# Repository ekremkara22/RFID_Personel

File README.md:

# RFID Personel Takip

RFID kart tabanli personel takip paneli. Bu repo web paneli, veritabani modeli ve ESP32/RFID cihaz entegrasyonu icin kullanilir; eski mobil uygulama kodlari devre disi birakilmistir.

## Birden fazla bilgisayarda çalışma

Her klonda bir kez çalıştırın:

```bash
git config core.hooksPath .githooks
```

Bundan sonra `git pull` ile `package-lock.json` değişirse `npm ci`, yalnız `prisma/schema.prisma` değişirse `npx prisma generate` otomatik çalışır. Veritabanı migration'ları otomatik uygulanmaz. Sunucularda bu ayar yapılmaz; deploy betikleri kurulumu zaten kendisi yapar.

## Getting Started

First, run the development server:

```bash
npm run dev
# or
yarn dev
# or
pnpm dev
# or
bun dev
```

Open [http://localhost:3000](http://localhost:3000) with your browser to see the result locally.

You can start editing the page by modifying `app/page.tsx`. The page auto-updates as you edit the file.

This project uses [`next/font`](https://nextjs.org/docs/app/building-your-application/optimizing/fonts) to automatically optimize and load [Geist](https://vercel.com/font), a new font family for Vercel.

## Learn More

To learn more about Next.js, take a look at the following resources:

- [Next.js Documentation](https://nextjs.org/docs) - learn about Next.js features and API.
- [Learn Next.js](https://nextjs.org/learn) - an interactive Next.js tutorial.

You can check out [the Next.js GitHub repository](https://github.com/vercel/next.js) - your feedback and contributions are welcome!

## Deploy on Vercel

The easiest way to deploy your Next.js app is to use the [Vercel Platform](https://vercel.com/new?utm_medium=default-template&filter=next.js&utm_source=create-next-app&utm_campaign=create-next-app-readme) from the creators of Next.js.

Check out our [Next.js deployment documentation](https://nextjs.org/docs/app/building-your-application/deploying) for more details.

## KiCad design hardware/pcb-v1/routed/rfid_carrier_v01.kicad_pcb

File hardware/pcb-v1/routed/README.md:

# RFID taşıyıcı PCB V0.2 — V4 kutu

Bu klasör V0.1 yerleşim taslağının bakır yolları çizilmiş prototip revizyonudur.
30 pin ESP32 DevKit V1 sökülebilir iki 1×15 dişi sokete takılır. Firmware GPIO
bağlantıları, V4 kart sınırı ve sekiz vida deliği korunur.

**Fiziksel prototip henüz üretilmedi veya çalıştırılmadı.** Dijital kontrollerin
sonuçları `drc.json` ve `erc.json` içindedir. Siparişten önce
aşağıdaki üç fiziksel kontrol yapılmalıdır; bu dosyalar ölçülmemiş parçaların
mekanik uyumunu garanti etmez.

## Açılacak dosyalar

- `rfid_carrier_v01.kicad_pro`: proje; dosya adı şema/PCB referanslarını korumak için sabit kaldı, revizyon V0.2'dir.
- `rfid_carrier_v01.kicad_pcb`: iki katmanlı bakır yolları, iki yüzde GND dolgusu ve
  serigrafi montaj işaretleri (pin-1 noktaları, elektrolitik `+`, D1 katot çizgisi, Q1 C/B/E).
- `rfid_carrier_v01.kicad_sch`: elektrik şeması; global hat adları PCB ile aynıdır.
- `pcb_routed.png`: gerçek PCB dosyasından KiCad ile üretilen üst yüz görünümü.
- `mechanical_1to1.svg`: kart sınırı, pedler, serigrafi ve parça zarfları; %100 baskı şablonu.
- `gerber/`: iki bakır, iki maske, iki baskı katmanı, kart sınırı, ayrı PTH/NPTH
  Excellon delik dosyaları, delik haritaları (PDF) ve `.gbrjob`.
- `drc.json`: Gerber'in üretildiği kartın KiCad DRC raporu.
- `connections.csv`, `bom.csv`: bağlantılar ve taşıyıcı kartın parça listesi.
- `native.net`: KiCad'in gerçek şemadan dışa aktardığı netlist.
- `RFID_Carrier.pretty/`, `RFID_Carrier.kicad_sym`, `*-lib-table`: proje ile taşınan yerel kütüphaneler.

Bir üst klasördeki V0.1 dosyaları ve eski inceleme PDF'si arşiv taslağıdır;
üretim için bu revizyonun dosyaları esas alınır.

## Tasarım kuralları ve değişiklikler

| Özellik | V0.2 |
|---|---|
| Kart | 128 × 58 mm, 1,6 mm, 2 katman; başlangıç 35 µm / 1 oz bakır |
| Kart koordinatları | V4 gövdesi normalize XY; X=4…132, Y=39…97 mm |
| Sinyal yolları | 0,30 mm |
| Güç yolları | 0,50 mm; GND ayrıca iki yüzeyde dolgu |
| Minimum elektriksel açıklık | 0,20 mm |
| Via | 1,00 mm bakır / 0,50 mm delik |
| ESP32 soket pedleri | 1,60 mm bakır / 1,00 mm delik; 2,54 mm adım |
| Soket sıra merkezleri | **25,40 mm varsayım — gerçek kartta ölçülecek** |
| Anten boşluğu | X=49…76, Y=39…85 mm; iki katmanda yol/via/dolgu yok |
| Vida boşlukları | 2,8 mm delikte 3,0 mm; 3,2 mm delikte 3,5 mm yarıçaplı bakırsız bölge |

V0.1'deki 0,80 mm güç yolu ve 0,25 mm açıklık önerisi bu yerleşimde soket
sıralarından geçişi engellediği için revize edildi. R7/R8 seri dirençleri ESP32
tarafına alındı; F1, C3, C5, Q1 ve RV1 montaj boşlukları düzeltildi. Güç
kaynakları şemada PWR_FLAG ile belirtildi. Kontroller için ihlal istisnası
eklenmedi. NPTH deliklerin koruma bölgesinde bulunabilmesi için bu bölgelerde
pad yasağı kullanılmaz; gerçek bileşen bakır pedleri ayrıca denetlenir.

## DRC durumu

DRC: 0 bağlantısız öğe, 0 şema–PCB farkı, 0 hata. Kalan 4 uyarı `starved_thermal`:
J6-2, U1-10, U1-19 ve C2-2 GND pedlerinin dolguya bağlanan termal kolu ikiden az.
Bu pedler GND'ye ayrıca bakır yolla bağlı olduğu için bilinçli olarak bırakıldı.

## Siparişten önce üç kontrol

1. **ESP32:** iki pin sırası merkezini ölçün; 25,40 mm olmalı. Üstten bakışta
   USB solda, anten sağda; J6 soldan VIN, J7 soldan 3V3 ile başlar. Kart
   etiketlerini `connections.csv` ile tek tek eşleştirin.
2. **Kutu:** `mechanical_1to1.svg` dosyasını gerçek boyut / %100 basın; kart
   sınırının 128 × 58 mm çıktığını cetvelle doğrulayın. Sekiz vida, kart sınırı, soket yüksekliği ve USB
   fişini V4 baskıda deneyin. PCB altı hedef Z=10 mm; mevcut USB penceresi
   yaklaşık Z=9…21 mm. Soket ESP32'yi yükselttiği için pencere değişikliği gerekebilir.
3. **BOM:** RV1 sürgü bacağı, J1 5,08 mm terminal, BC337 C-B-E, elektrolitik
   çap/adım, RN1 ortak bacak ve seçilen dişi soketlerin gövdelerini kontrol edin.
   J2…J5 genel 2,54 mm pin sıralarıdır; kilitli konnektör gövdeleri doğrulanmadı.

## Montaj ve ilk çalıştırma

- J1 yalnız **regüle 5 V DC** içindir. 12 V girişi, ters kutup koruması ve USB
  ile harici güç arasında otomatik seçim devresi yoktur. İlk programlamada
  ESP32'yi taşıyıcıdan çıkarıp USB ile programlayın. Harici beslemeyle kullanımda JP1 takılır.
- U1 **SN74AHCT244N DIP-20** olmalıdır. RN1 ortak ucu pin 1 olan 8×10 kΩ
  bussed SIP-9 ağıdır. LCD paralel 4-bit arayüz kullanır; I2C adaptör gerekmez.
- J2 RC522 sadece 3,3 V'tur. Soket sırası isimle eşleştirilir; kablo renkleri
  esas alınmaz. RFID kablosunu kısa tutun. Uzun bakır hatların/kablonun gerçek
  SPI okuma kararlılığı donanım üzerinde denenmelidir.
- R5=330 Ω LCD arka ışığı için başlangıç değeridir; ekranın gerçek akımı ve
  dahili direnci ölçülmeden köprülemeyin. Buzzer, Q1 ve D1 uygunluğu gerçek
  buzzer akımına bağlıdır. F1'in 0,75 A değeri kart için doğrulanmış akım kapasitesi değildir.
- Önce modüller çıkarılmışken kısa devre ve kutup kontrolü yapın. Akım sınırlı
  5 V ile besleyin; sonra gücü kesip ESP32, ekran, RC522 ve buzzerı sırayla ekleyin.
  Wi-Fi + arka ışık + buzzer eşzamanlı çalışırken 5 V / 3V3 düşümünü, resetleri,
  sıcaklığı ve kapak kapalı RFID menzilini kontrol edin.

## Doğrulama ve yeniden üretme

Doğrulama için resmi imzalı KiCad **10.99.0-4384-g95775e4647** CLI kullanıldı.
PCB/şema kaynakları KiCad 8 dosya sözdizimini korur; KiCad 8 uygulamasıyla
ayrıca denenmedi. Freerouting yerel çalıştırıldı; tasarım harici yönlendirme
servisine yüklenmedi. Donanım güç/ısı, sinyal bütünlüğü veya RF laboratuvar testi yapılmadı.

`prepare.py` yerleşim ve şema kaynağını üretir ve **mevcut bakır yollarını siler**.
`export_dsn.py` yönlendirme girdisini, `import_ses.py` SES'ten bakır yollarını
oluşturur. `finish_board.py` GND bölgelerini ekler; dolgu KiCad tarafından
yapılır. `add_silk_marks.py` dolgudan sonra serigrafi montaj işaretlerini ekler. `review.py` gerçek PCB dosyasından kontrol raporu ve görsel üretir.
El ile düzenlenmiş PCB üzerine `prepare.py` çalıştırmayın.

Şema değişikliğinde ERC, şema–PCB netlist karşılaştırması ve DRC; her PCB
değişikliğinde dolgu yenileme, tüm DRC kontrolleri ve Gerber/delik dışa aktarımı
tekrarlanmalıdır. `validation.json` içindeki SHA-256, raporun hangi PCB'ye ait
olduğunu gösterir.

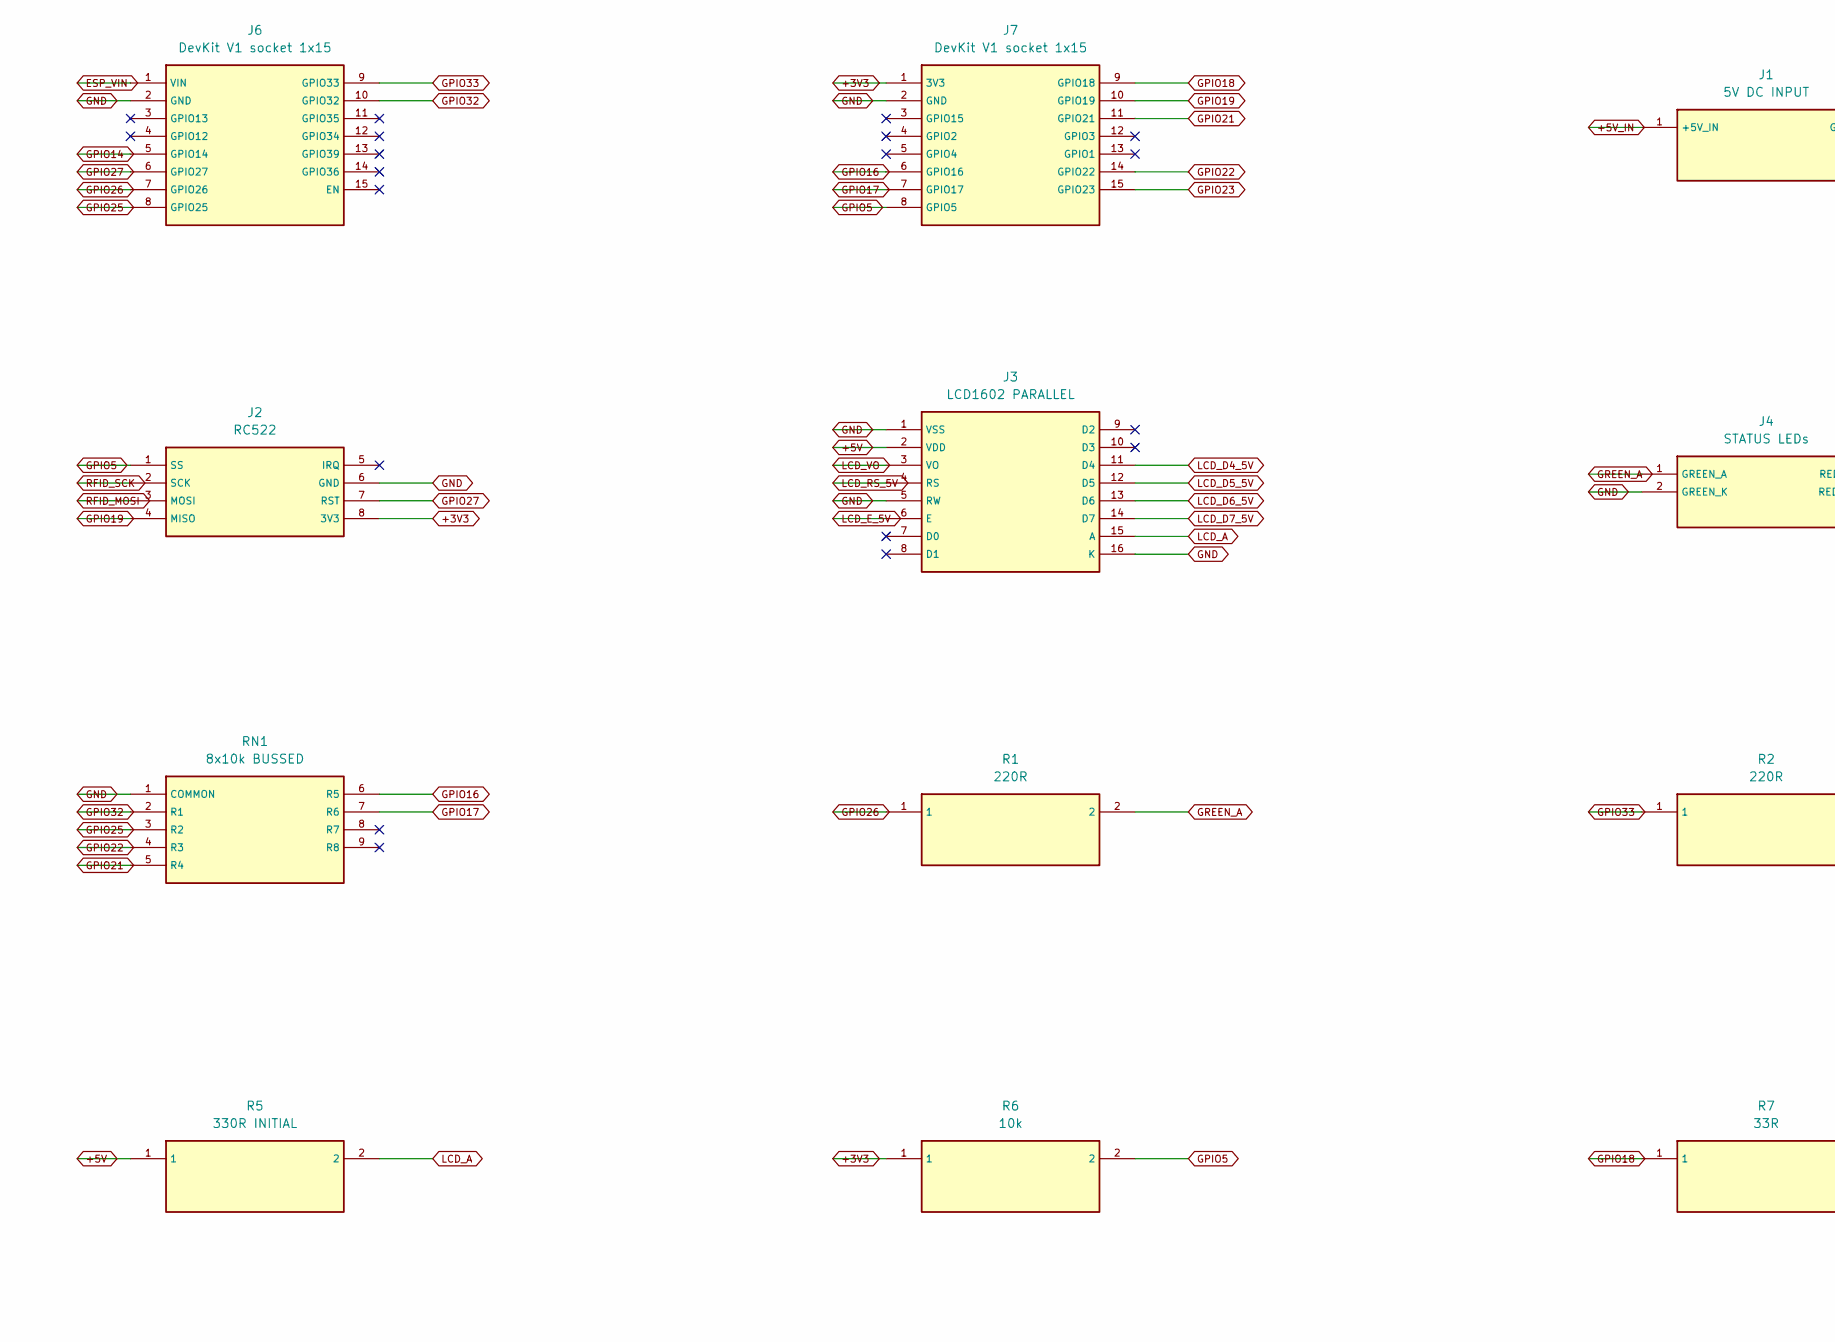
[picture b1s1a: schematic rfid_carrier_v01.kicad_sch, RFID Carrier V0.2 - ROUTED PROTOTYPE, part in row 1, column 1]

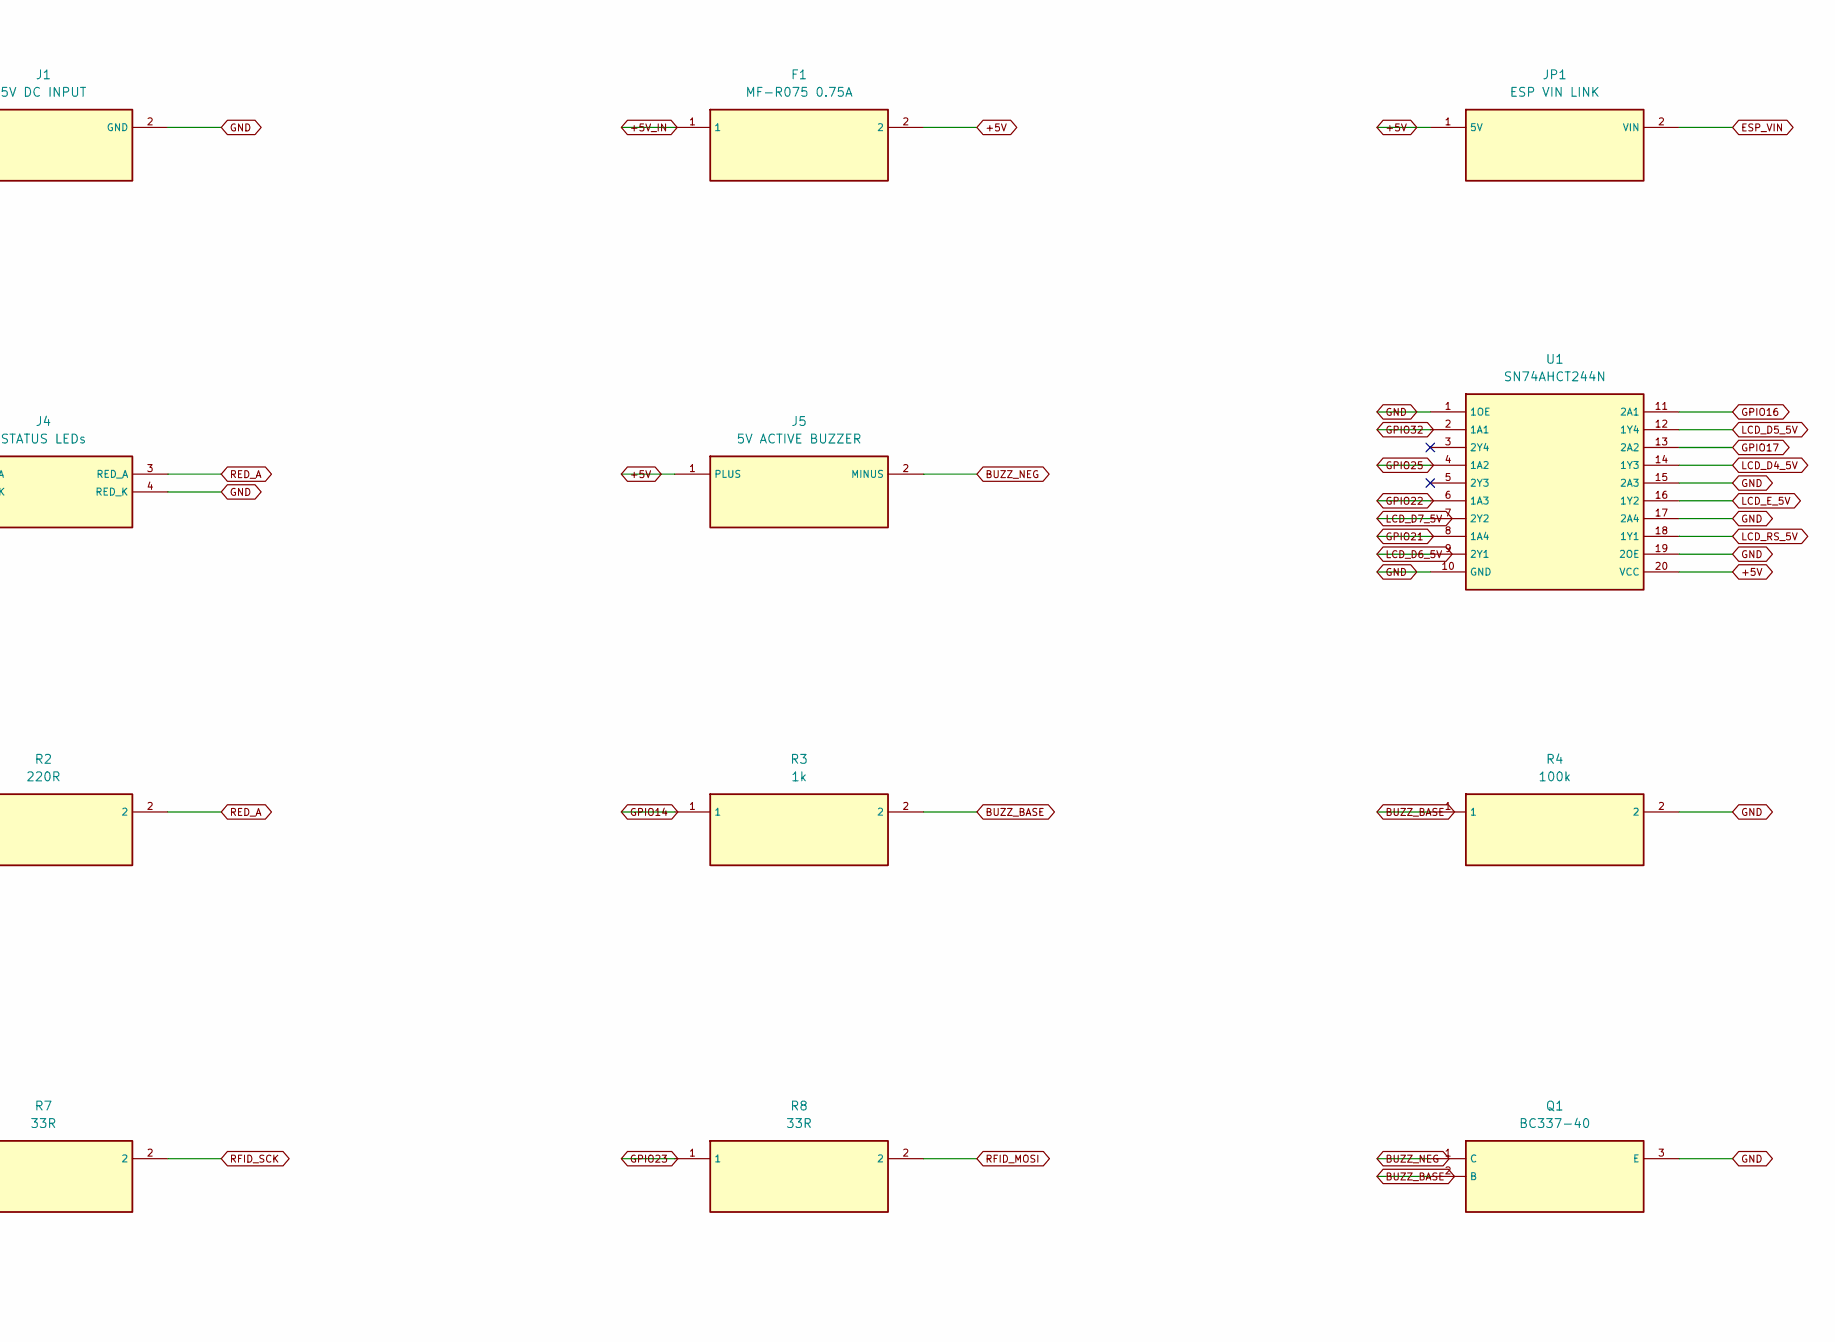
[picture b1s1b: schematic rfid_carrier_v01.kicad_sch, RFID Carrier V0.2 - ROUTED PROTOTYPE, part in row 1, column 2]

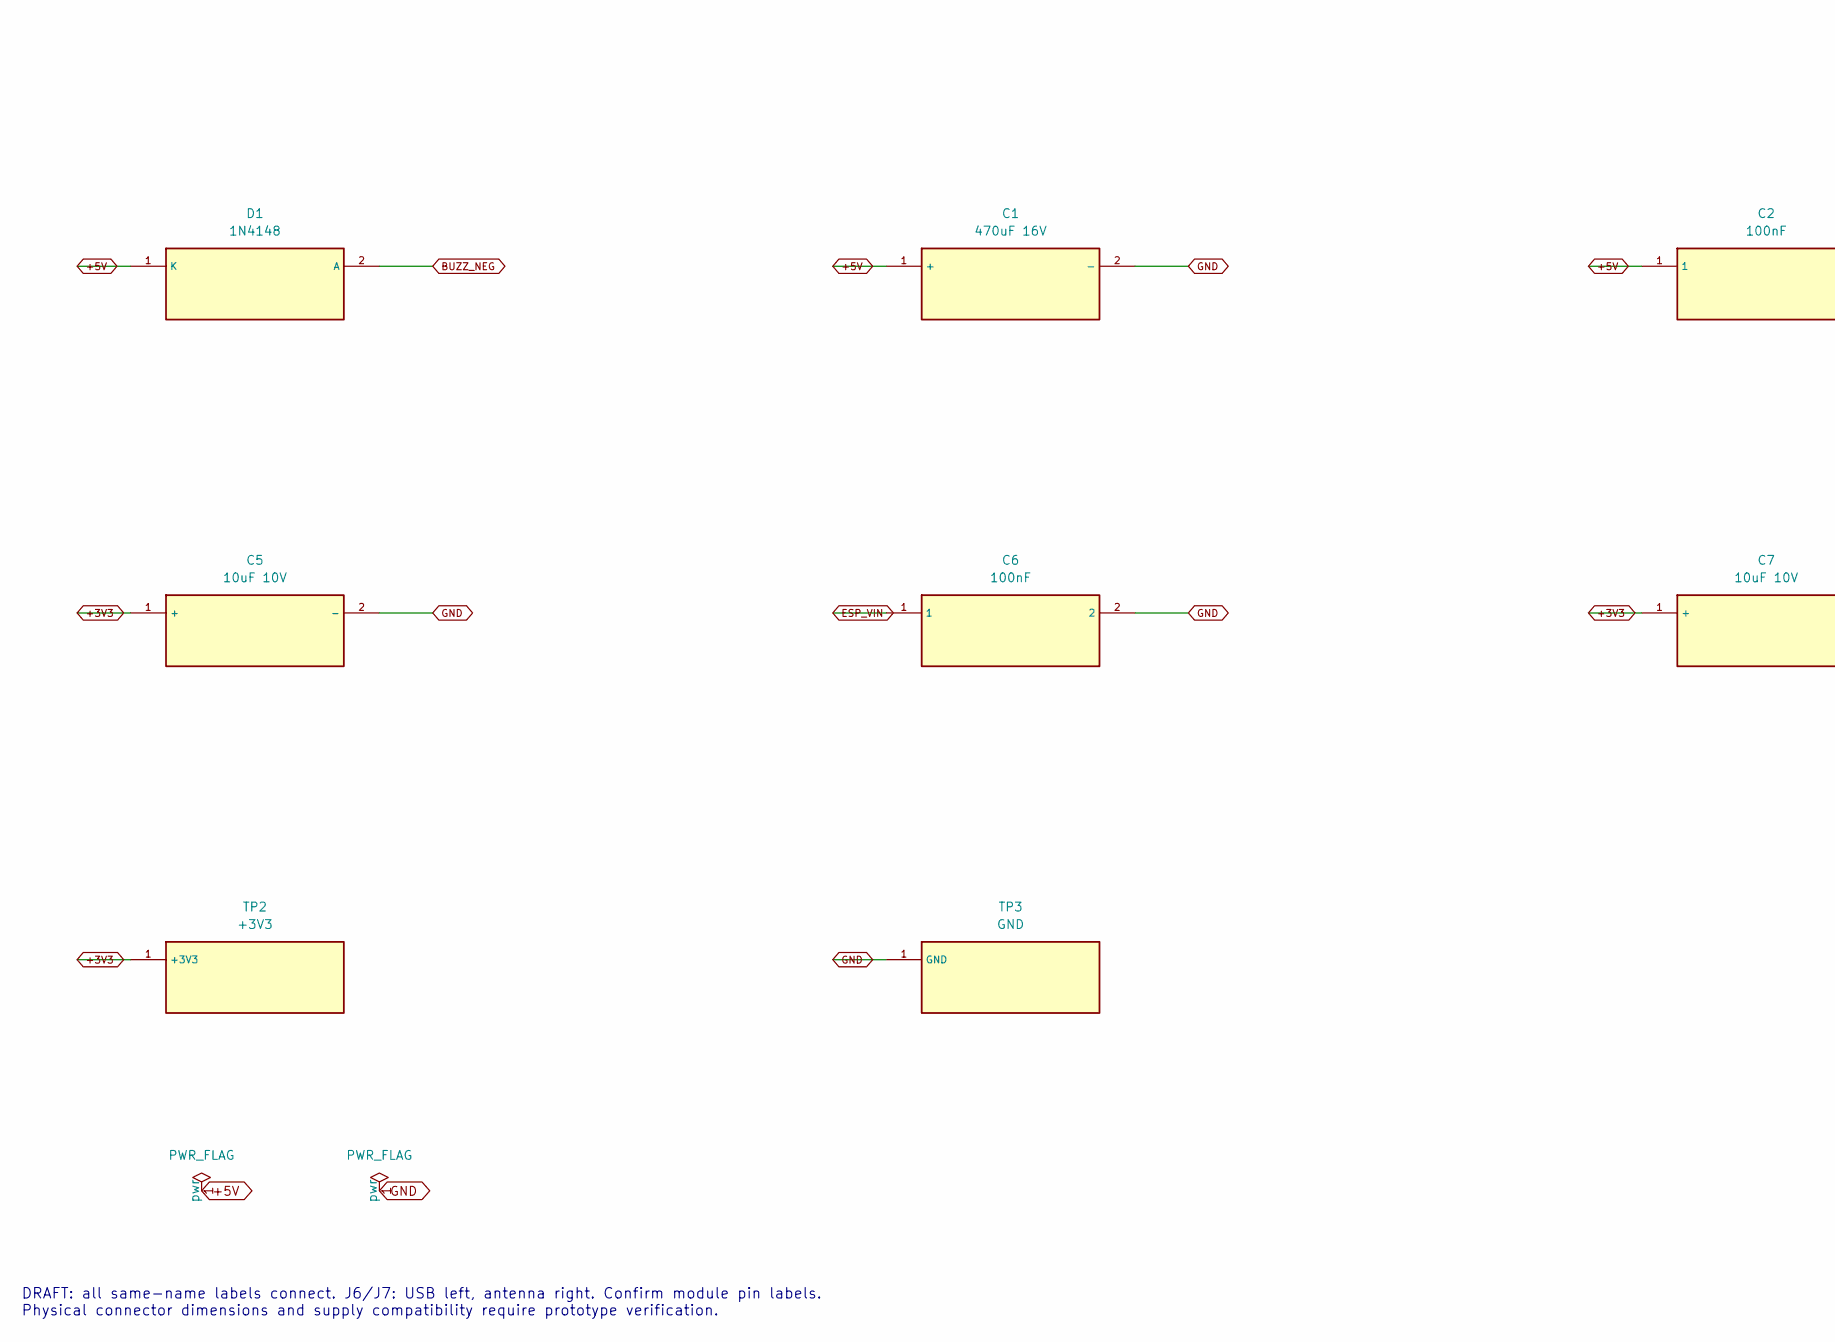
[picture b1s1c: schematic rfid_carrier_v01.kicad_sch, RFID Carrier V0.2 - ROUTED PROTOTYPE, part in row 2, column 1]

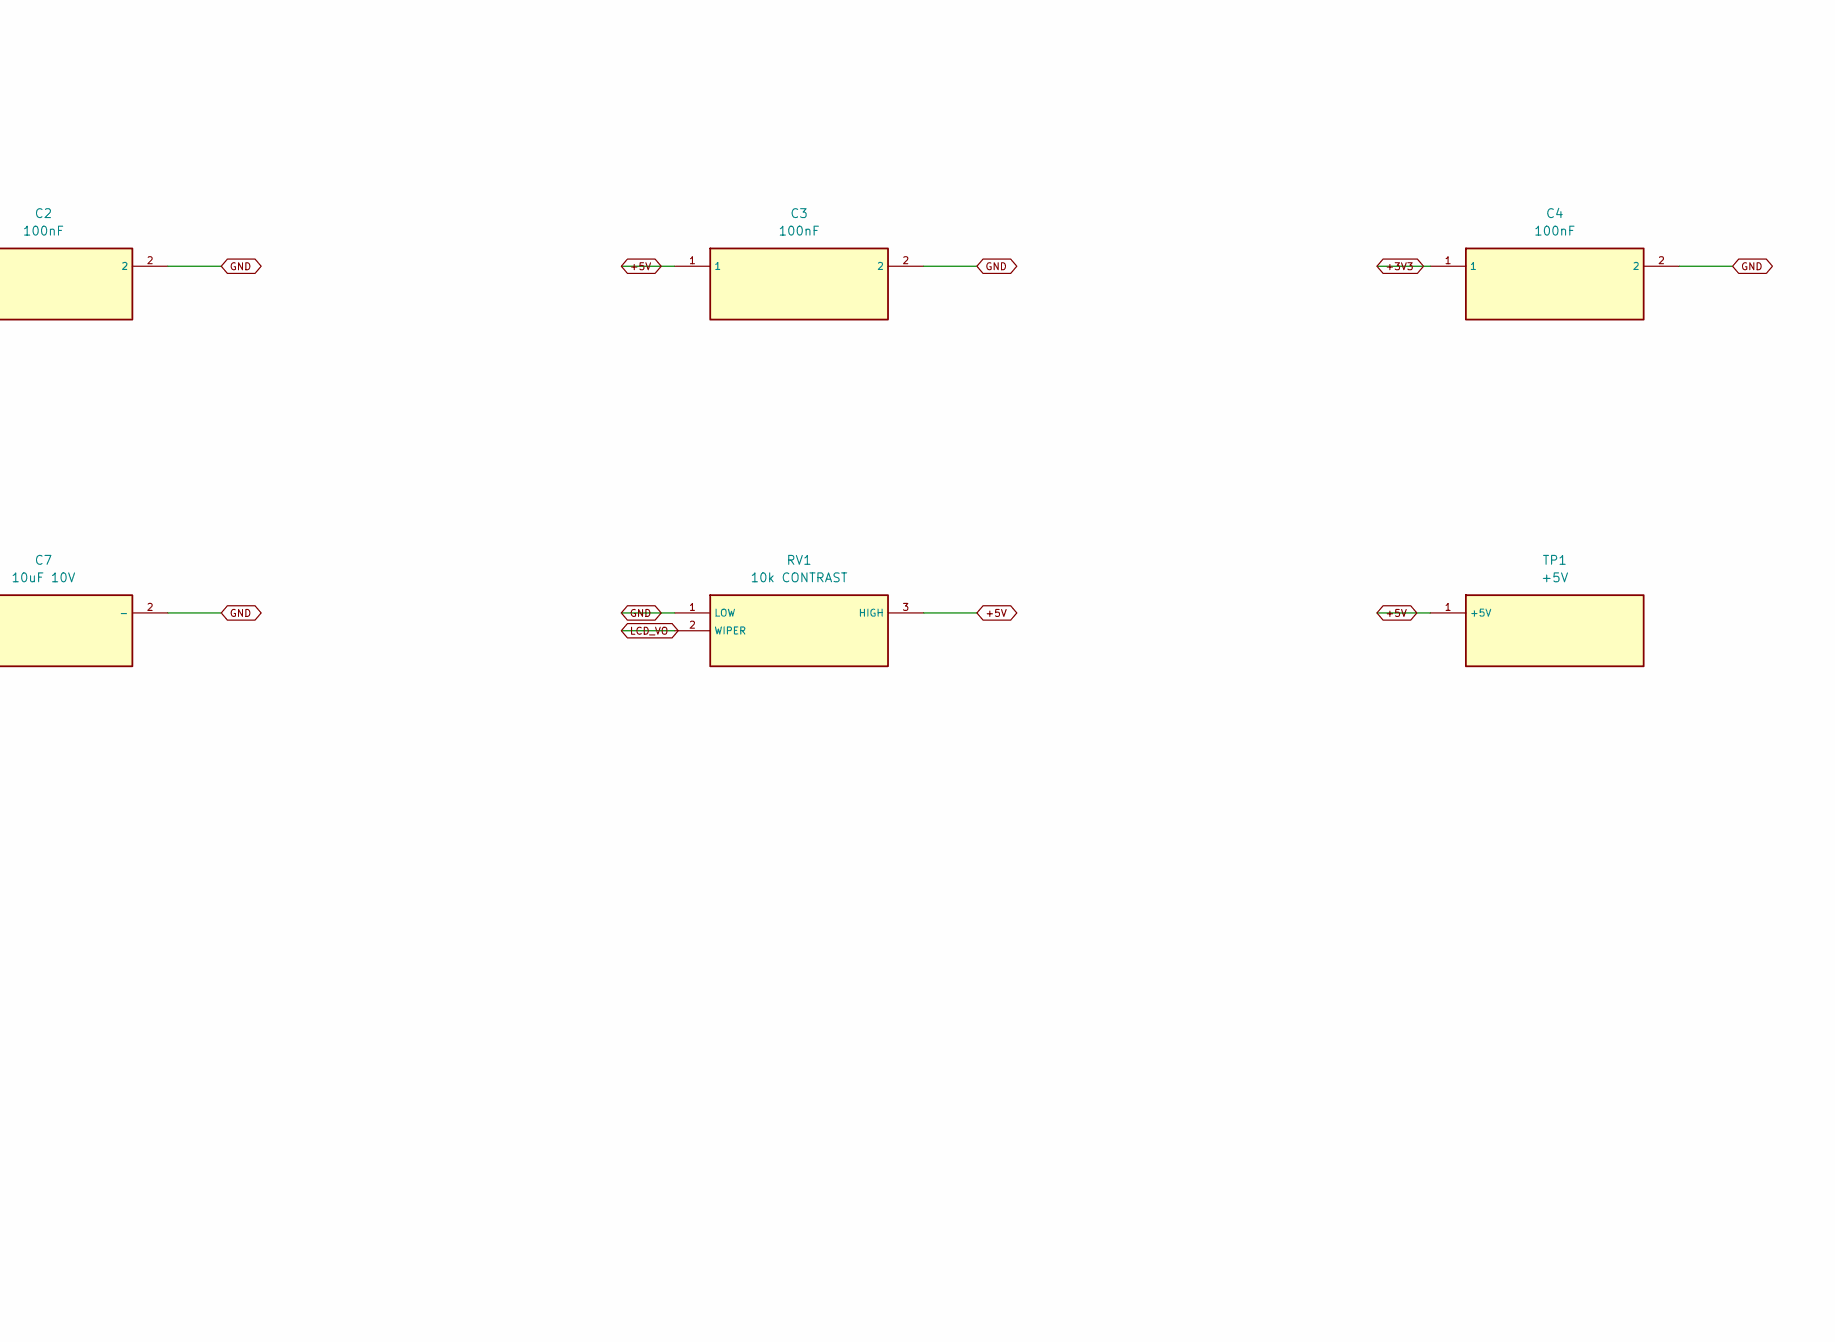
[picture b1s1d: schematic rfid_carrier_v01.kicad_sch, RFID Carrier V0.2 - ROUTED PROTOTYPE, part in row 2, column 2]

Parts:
C1: 470uF 16V; C1_CP_P3.5_H
C2: 100nF; C2_C_P2.54_H
C3: 100nF; C3_C_P2.54_H
C4: 100nF; C4_C_P2.54_H
C5: 10uF 10V; C5_CP_P2_H
C6: 100nF; C6_C_P2.54_H
C7: 10uF 10V; C7_CP_P2_H
D1: 1N4148; D1_D_P7.62_H
F1: MF-R075 0.75A; F1_PTC_P5.08_H
J1: 5V DC INPUT; J1_Header_2_P5.08_V
J2: RC522; J2_Header_8_P2.54_H
J3: LCD1602 PARALLEL; J3_Header_16_P2.54_H
J4: STATUS LEDs; J4_Header_4_P2.54_H
J5: 5V ACTIVE BUZZER; J5_Header_2_P2.54_H
J6: DevKit V1 socket 1x15; J6_Header_15_P2.54_H
J7: DevKit V1 socket 1x15; J7_Header_15_P2.54_H
JP1: ESP VIN LINK; JP1_Header_2_P2.54_V
Q1: BC337-40; Q1_TO92_CBE_FORMED_P2.54
R1: 220R; R1_R_P7.62_V
R2: 220R; R2_R_P7.62_V
R3: 1k; R3_R_P7.62_H
R4: 100k; R4_R_P7.62_H
R5: 330R INITIAL; R5_R_P7.62_H
R6: 10k; R6_R_P7.62_H
R7: 33R; R7_R_P7.62_V
R8: 33R; R8_R_P7.62_V
RN1: 8x10k BUSSED; RN1_Header_9_P2.54_V
RV1: 10k CONTRAST; RV1_Trimmer_3pin_5.08x2.54
TP1: +5V; TP1_TestPoint_THT
TP2: +3V3; TP2_TestPoint_THT
TP3: GND; TP3_TestPoint_THT
U1: SN74AHCT244N; U1_DIP20_W7.62

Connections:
+3V3: C4.1, C5.1 (+), C7.1 (+), J2.8 (3V3), J7.1 (3V3), R6.1, TP2.1
+5V: C1.1 (+), C2.1, C3.1, D1.1 (K), F1.2, J3.2 (VDD), J5.1 (PLUS), JP1.1 (5V), R5.1, RV1.3 (HIGH), TP1.1, U1.20 (VCC)
+5V_IN: F1.1, J1.1 (+5V_IN)
BUZZ_BASE: Q1.2 (B), R3.2, R4.1
BUZZ_NEG: D1.2 (A), J5.2 (MINUS), Q1.1 (C)
ESP_VIN: C6.1, J6.1 (VIN), JP1.2 (VIN)
GND: C1.2 (-), C2.2, C3.2, C4.2, C5.2 (-), C6.2, C7.2 (-), J1.2 (GND), J2.6 (GND), J3.1 (VSS), J3.5 (RW), J3.16 (K), J4.2 (GREEN_K), J4.4 (RED_K), J6.2 (GND), J7.2 (GND), Q1.3 (E), R4.2, RN1.1 (COMMON), RV1.1 (LOW), TP3.1, U1.1 (1OE), U1.10 (GND), U1.15 (2A3), U1.17 (2A4), U1.19 (2OE)
GPIO5: J2.1 (SS), J7.8 (GPIO5), R6.2
GPIO14: J6.5 (GPIO14), R3.1
GPIO16: J7.6 (GPIO16), RN1.6 (R5), U1.11 (2A1)
GPIO17: J7.7 (GPIO17), RN1.7 (R6), U1.13 (2A2)
GPIO18: J7.9 (GPIO18), R7.1
GPIO19: J2.4 (MISO), J7.10 (GPIO19)
GPIO21: J7.11 (GPIO21), RN1.5 (R4), U1.8 (1A4)
GPIO22: J7.14 (GPIO22), RN1.4 (R3), U1.6 (1A3)
GPIO23: J7.15 (GPIO23), R8.1
GPIO25: J6.8 (GPIO25), RN1.3 (R2), U1.4 (1A2)
GPIO26: J6.7 (GPIO26), R1.1
GPIO27: J2.7 (RST), J6.6 (GPIO27)
GPIO32: J6.10 (GPIO32), RN1.2 (R1), U1.2 (1A1)
GPIO33: J6.9 (GPIO33), R2.1
GREEN_A: J4.1 (GREEN_A), R1.2
LCD_A: J3.15 (A), R5.2
LCD_D4_5V: J3.11 (D4), U1.14 (1Y3)
LCD_D5_5V: J3.12 (D5), U1.12 (1Y4)
LCD_D6_5V: J3.13 (D6), U1.9 (2Y1)
LCD_D7_5V: J3.14 (D7), U1.7 (2Y2)
LCD_E_5V: J3.6 (E), U1.16 (1Y2)
LCD_RS_5V: J3.4 (RS), U1.18 (1Y1)
LCD_VO: J3.3 (VO), RV1.2 (WIPER)
RED_A: J4.3 (RED_A), R2.2
RFID_MOSI: J2.3 (MOSI), R8.2
RFID_SCK: J2.2 (SCK), R7.2

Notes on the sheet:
DRAFT: all same-name labels connect. J6/J7: USB left, antenna right. Confirm module pin labels. Physical connector dimensions and supply compatibility require prototype verification.

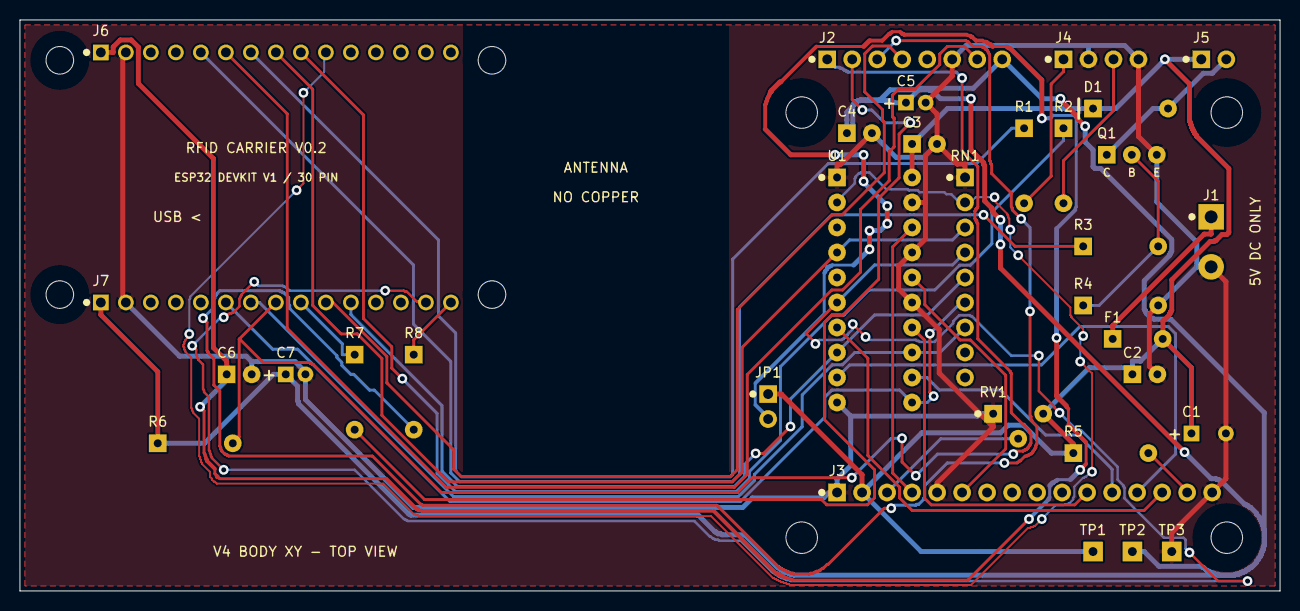
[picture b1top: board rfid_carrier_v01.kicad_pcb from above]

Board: 2 copper layers, 128.0 x 58.0 mm, 40 parts (0 on the bottom side), 33 nets.

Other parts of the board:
H1, H2, H3, H4: MountingHole_2.8mm
H5, H6, H7, H8: MountingHole_3.2mm

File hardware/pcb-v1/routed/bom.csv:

Reference,Qty,Value,Footprint,Notes
J6,1,DevKit V1 socket 1x15,J6_Header_15_P2.54_H,ASSUMED 25.40 mm row spacing; 2.54 mm pitch. Confirm labels and orientation on actual board.
J7,1,DevKit V1 socket 1x15,J7_Header_15_P2.54_H,ASSUMED 25.40 mm row spacing; 2.54 mm pitch. Confirm labels and orientation on actual board.
J1,1,5V DC INPUT,J1_Header_2_P5.08_V,"2-pin 5.08 mm terminal block; body envelope provisional; regulated 5V only, no reverse-polarity protection."
F1,1,MF-R075 0.75A,F1_PTC_P5.08_H,Bourns MF-R075 nominal 5.1 mm leads; current/temperature derating and voltage drop need measurement.
JP1,1,ESP VIN LINK,JP1_Header_2_P2.54_V,Fit shunt for normal external power. Not a USB power multiplexer; program removed module for first bring-up.
J2,1,RC522,J2_Header_8_P2.54_H,"Match signal NAMES on reader, not cable colours. 3.3V only; IRQ unused."
J3,1,LCD1602 PARALLEL,J3_Header_16_P2.54_H,16-pin ribbon cable. Pin 1 at LEFT in this PCB view. LCD backlight must remain current limited.
J4,1,STATUS LEDs,J4_Header_4_P2.54_H,
J5,1,5V ACTIVE BUZZER,J5_Header_2_P2.54_H,
U1,1,SN74AHCT244N,U1_DIP20_W7.62,Use AHCT or separately verified HCT; ordinary HC at 5V is not an equivalent 3.3V-input replacement. Both OE pins grounded.
RN1,1,8x10k BUSSED,RN1_Header_9_P2.54_V,"SIP-9, eight resistors sharing pin 1. NOT an isolated network. Spare pins 8/9 unconnected."
R1,1,220R,R1_R_P7.62_V,
R2,1,220R,R2_R_P7.62_V,
R3,1,1k,R3_R_P7.62_H,
R4,1,100k,R4_R_P7.62_H,
R5,1,330R INITIAL,R5_R_P7.62_H,"Safe dim starting value, adjust ONLY from backlight specifications/measured current. Never blindly bridge."
R6,1,10k,R6_R_P7.62_H,SS idle high; boot-strapping GPIO5 must remain compatible with actual DevKit.
R7,1,33R,R7_R_P7.62_V,SPI clock series damping; verify waveforms/read reliability after routing.
R8,1,33R,R8_R_P7.62_V,SPI MOSI series damping; keep RC522 harness short.
Q1,1,BC337-40,Q1_TO92_CBE_FORMED_P2.54,"onsemi C-B-E reference; formed 2.54 mm leads, check actual transistor. 1k base resistor assumes a small buzzer; measure current."
D1,1,1N4148,D1_D_P7.62_H,"Pin 1=CATHODE, stripe at +5V; pin 2=ANODE at buzzer negative. Verify rating for actual buzzer."
C1,1,470uF 16V,C1_CP_P3.5_H,"Radial electrolytic, assumed diameter 8 mm and lead pitch 3.5 mm. Check actual part and polarity."
C2,1,100nF,C2_C_P2.54_H,
C3,1,100nF,C3_C_P2.54_H,
C4,1,100nF,C4_C_P2.54_H,
C5,1,10uF 10V,C5_CP_P2_H,"Radial electrolytic, assumed diameter 5 mm and lead pitch 2 mm. Check actual part and polarity."
C6,1,100nF,C6_C_P2.54_H,
C7,1,10uF 10V,C7_CP_P2_H,"Radial electrolytic, assumed diameter 5 mm and lead pitch 2 mm. Check actual part and polarity."
RV1,1,10k CONTRAST,RV1_Trimmer_3pin_5.08x2.54,"Provisional trimmer footprint, verify model AND wiper pin before order."
TP1,1,+5V,TP1_TestPoint_THT,
TP2,1,+3V3,TP2_TestPoint_THT,
TP3,1,GND,TP3_TestPoint_THT,

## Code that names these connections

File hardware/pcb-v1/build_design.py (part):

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
# Explicit local pin numbers, not an undocumented library's module numbering.
# Top view: USB LEFT, antenna RIGHT. Each row numbered LEFT to RIGHT.
upper=['VIN','GND','GPIO13','GPIO12','GPIO14','GPIO27','GPIO26','GPIO25','GPIO33','GPIO32','GPIO35','GPIO34','GPIO39','GPIO36','EN']
lower=['3V3','GND','GPIO15','GPIO2','GPIO4','GPIO16','GPIO17','GPIO5','GPIO18','GPIO19','GPIO21','GPIO3','GPIO1','GPIO22','GPIO23']
used={5,14,16,17,18,19,21,22,23,25,26,27,32,33}
def espnet(pin):
    if pin=='VIN': return 'ESP_VIN'
    if pin=='3V3': return '+3V3'
    if pin=='GND': return 'GND'
    return pin if pin.startswith('GPIO') and int(pin[4:]) in used else None
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PARTS[-1]['body']=[112.34,69.4,122.74,72.6]
row('JP1','ESP VIN LINK',80,77,[('5V','+5V'),('VIN','ESP_VIN')],vertical=True,
    note='Fit shunt for normal external power. Not a USB power multiplexer; program removed module for first bring-up.')
row('J2','RC522',86,43,[('SS','GPIO5'),('SCK','RFID_SCK'),('MOSI','RFID_MOSI'),('MISO','GPIO19'),('IRQ',None),('GND','GND'),('RST','GPIO27'),('3V3','+3V3')],
    note='Match signal NAMES on reader, not cable colours. 3.3V only; IRQ unused.')
row('J3','LCD1602 PARALLEL',87,87,[('VSS','GND'),('VDD','+5V'),('VO','LCD_VO'),('RS','LCD_RS_5V'),('RW','GND'),('E','LCD_E_5V'),('D0',None),('D1',None),('D2',None),('D3',None),('D4','LCD_D4_5V'),('D5','LCD_D5_5V'),('D6','LCD_D6_5V'),('D7','LCD_D7_5V'),('A','LCD_A'),('K','GND')],
    note='16-pin ribbon cable. Pin 1 at LEFT in this PCB view. LCD backlight must remain current limited.')
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u_types={i:('power_in' if i in [10,20] else 'tri_state' if i in [3,5,7,9,12,14,16,18] else 'input') for i in range(1,21)}
add('U1','SN74AHCT244N',u_pins,u_pads,[85.92,53.73,95.7,79.13],'DIP20_W7.62',
    'Use AHCT or separately verified HCT; ordinary HC at 5V is not an equivalent 3.3V-input replacement. Both OE pins grounded.',u_types)
row('RN1','8x10k BUSSED',100,55,[('COMMON','GND'),('R1','GPIO32'),('R2','GPIO25'),('R3','GPIO22'),('R4','GPIO21'),('R5','GPIO16'),('R6','GPIO17'),('R7',None),('R8',None)],vertical=True,
    note='SIP-9, eight resistors sharing pin 1. NOT an isolated network. Spare pins 8/9 unconnected.')
two('R1','220R',106,50,'GPIO26','GREEN_A',vertical=True)
two('R2','220R',110,50,'GPIO33','RED_A',vertical=True)
two('R3','1k',112,62,'GPIO14','BUZZ_BASE')
two('R4','100k',112,68,'BUZZ_BASE','GND')
two('R5','330R INITIAL',111,83,'+5V','LCD_A',note='Safe dim starting value, adjust ONLY from backlight specifications/measured current. Never blindly bridge.')
two('R6','10k',39,82,'+3V3','GPIO5',note='SS idle high; boot-strapping GPIO5 must remain compatible with actual DevKit.')
two('R7','33R',20,82,'GPIO18','RFID_SCK',note='SPI clock series damping; verify waveforms/read reliability after routing.')
two('R8','33R',8,82,'GPIO23','RFID_MOSI',note='SPI MOSI series damping; keep RC522 harness short.')
add('Q1','BC337-40', [('C','BUZZ_NEG'),('B','BUZZ_BASE'),('E','GND')],
    [(115,53,1.8,.8),(117.54,53,1.8,.8),(120.08,53,1.8,.8)], [114,50.5,121.08,55.5], 'TO92_CBE_FORMED_P2.54',
    'onsemi C-B-E reference; formed 2.54 mm leads, check actual transistor. 1k base resistor assumes a small buzzer; measure current.')
two('D1','1N4148',113,48,'+5V','BUZZ_NEG',kind='D',note='Pin 1=CATHODE, stripe at +5V; pin 2=ANODE at buzzer negative. Verify rating for actual buzzer.')
PARTS[-1]['pins'][0]['name']='K'; PARTS[-1]['pins'][1]['name']='A'

def cap(ref,val,x,y,rail,pitch=2.54,diam=None):
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    test('LCD RW grounded',pins[('J3','5')]=='GND')
    test('AHCT unused inputs grounded',pins[('U1','15')]==pins[('U1','17')]=='GND')
    test('AHCT enables grounded',pins[('U1','1')]==pins[('U1','19')]=='GND')
    test('Buzzer diode cathode +5V',pins[('D1','1')]=='+5V' and pins[('D1','2')]=='BUZZ_NEG')
    firmware=(ROOT/'esp32-device/rfid_personel_device/rfid_personel_device.ino').read_text(encoding='utf-8-sig')
    expected={'RFID_SS_PIN':5,'RFID_RST_PIN':27,'GREEN_LED_PIN':26,'RED_LED_PIN':33,'BUZZER_PIN':14,'LCD_RS_PIN':32,'LCD_ENABLE_PIN':25,'LCD_D4_PIN':22,'LCD_D5_PIN':21,'LCD_D6_PIN':16,'LCD_D7_PIN':17}
    test('Firmware GPIO defines match',all(re.search(r'#define\s+'+name+r'\s+'+str(value)+r'\b',firmware) for name,value in expected.items()))
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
